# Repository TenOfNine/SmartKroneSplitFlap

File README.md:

# KRONE REW Fallblattanzeige — Ersatzsteuerung

Eigenbau-Steuerung für eine mechanische Fallblattanzeige der KRONE AG aus dem Jahr 1990. Die Original-Elektronik (Anzeigersteuerung und Palettensteuerungen PST mit HMCS44C) wird ersetzt. Mechanik und Anzeigenplatinen bleiben unverändert.

## Aufbau

```
ESP32-C3 (Master, WLAN/REST/MQTT)
  └─ RS-485 half duplex + CHAIN
       ├─ Daughter Card 1 (ATtiny1616) ── Anzeigenmodul 1
       ├─ Daughter Card 2 ────────────── Anzeigenmodul 2
       └─ …                                        bis 10
```

Jedes Anzeigenmodul erhält eine eigene kleine Steuerplatine, die die Hall-Impulse zählt, den Triac ansteuert und die aktuelle Blattposition kennt. Die Adressvergabe erfolgt automatisch entlang einer CHAIN-Leitung, sodass die Adresse der physischen Position entspricht und ein Kartentausch keine Einstellung erfordert.

## Eckdaten

| Größe | Wert |
|---|---|
| Anzeigenmodule | 10, Palettenmodulreihe A, Modulgröße 1 |
| Blätter je Modul | 40 |
| Zeichensatz | Leerbild, 0–9, A–Z, `-`, `.` |
| Zeit je Blatt | 60 ms, volle Umdrehung 2,40 s |
| Motor | Berger RSM 42/12, 42 V~, 250 U/min |
| Triac | Teccor L201E3, sensitives Gate |
| Modul-CPU | ATtiny1616 |
| Bus | RS-485, 115200 Bd, TP8485E |
| Master | ESP32-C3 Super Mini auf Trägerboard |

## Verzeichnisse

| Pfad | Inhalt |
|---|---|
| `docs/` | Spezifikation, Schaltpläne, Backlog, Toolchain, Symbolprüfungen, Prüfpunkte, Messprotokolle |
| `hardware/daughtercard/` | KiCad-Projekt der Modulsteuerung (geroutet, Fertigungspaket) |
| `hardware/master/` | KiCad-Projekt der Zentralsteuerung (geroutet, Fertigungspaket) |
| `firmware/module/` | ATtiny1616, PlatformIO |
| `firmware/master/` | ESP32-C3, PlatformIO (inkl. Web-UI, `prebuilt/` Flash-Image) |
| `tools/` | Setup, Schaltplan-/PCB-Generatoren, Router-Anbindung, Bus-Testwerkzeug |
| `reference/` | **Nicht versioniert.** Ablage für die Original-Herstellerunterlagen. |

## Stand

| Bereich | Stand |
|---|---|
| Spezifikation, Schaltplan (Netzliste) | vollständig, `docs/` |
| Schaltplan `.kicad_sch` + Footprints + PCB-Netzliste | generiert, ERC 0/0 (Daughter Card + Master) |
| PCB-Layout `.kicad_pcb` | geroutet, DRC 0 Fehler (in der CI geprüft); Daughter Cards und Zentralsteuerung gefertigt, Inbetriebnahme am Gerät läuft (`docs/progress.md`) |
| Modul-Firmware (ATtiny1616) | `firmware/module/`, Version siehe `firmware/CHANGELOG.md`; Bootloader für die Verteilung über den Bus |
| Master-Firmware (ESP32-C3 Super Mini) | `firmware/master/`, Web-UI, REST, MQTT, OTA — Web-Flasher siehe unten |
| Bus-Werkzeug | `tools/busctl.py` |
| CI | `.github/workflows/ci.yml`: Host-Tests, Firmware-Builds mit Abgleich der Prebuilts gegen die Quelle, ERC/DRC, Release-Paket je Tag |
| Offene Messungen O-2, O-5, O-6 | parametrisiert, blockieren die Fertigung nicht |

Der Projektstand für den Einstieg in eine neue Arbeitssitzung steht in
`docs/projektstand.md`.

## Einstieg

```bash
bash tools/setup.sh                              # Toolchain, siehe docs/toolchain.md
source .venv/bin/activate

pio test -e native -d firmware/module            # 163 Tests
pio test -e native -d firmware/master            # 137 Tests
python tools/test_busctl.py                      # 16 Tests + Rahmen-Selbsttest
python tools/gen_daughtercard_sch.py --erc --pdf --png
```

## Firmware flashen

**Master (ESP32-C3 Super Mini).** Am einfachsten über den Browser-Flasher:
**<https://tenofnine.github.io/SmartKroneSplitFlap/>**

Nötig: Chrome oder Edge auf dem Desktop, ein USB-C-Kabel **mit Datenadern** an
die Buchse des Moduls. „Modul verbinden & flashen" drücken — der C3 geht selbst
in den Download-Modus, kein BOOT-Taster. Nach dem Flashen öffnet die Karte den
Access-Point `krone_anzeige` für die WLAN-Zugangsdaten. Das fertige Image liegt
committet unter `firmware/master/prebuilt/`; neu bauen mit
`python tools/build_master_firmware.py` oder direkt
`pio run -e esp32c3 -t upload -d firmware/master`.

Die Web-Oberfläche vorab ansehen — dieselbe Seite mit Beispieldaten und
simuliertem Bus, ohne Gerät:
**<https://tenofnine.github.io/SmartKroneSplitFlap/demo/>**
(erzeugt aus `firmware/master/src/main.cpp` per `python tools/build_webui_demo.py`).

Spätere Updates laufen über die Web-UI (*Einstellungen › Firmware aktualisieren*):
den **signierten Container** `firmware/master/prebuilt/krone-master-esp32c3.kota`
hochladen. Das Modul verlangt eine gültige ECDSA-Signatur des Projektschlüssels —
Einrichtung siehe [`docs/firmware-signing.md`](docs/firmware-signing.md). Der
Zugriff auf Web-UI/REST ist ab Werk auf private Netze beschränkt und lässt sich
mit einem Passwort schützen (*Einstellungen › Zugriffsschutz*).

**Daughter Card (ATtiny1616).** Über die UPDI-Stiftleiste J6 mit einem
USB-Seriell-Adapter (FTDI/CP2102/CH340, **auf 5 V**) und einem 4,7-kΩ-Widerstand
zwischen TXD und RXD:

```
  USB-Seriell-Adapter                       Daughter Card J6 (1×3)
  ┌───────────────┐
  │           GND ●──────────────────────────────● 1  GND
  │           TXD ●────[ 4,7 kΩ ]───┬────────────● 2  UPDI   (→ ATtiny PA0)
  │           RXD ●─────────────────┘
  │        5V/VCC ●──────────────────────────────● 3  +5V
  └───────────────┘        └─ nur wenn die Karte sonst keine 5 V hat
```

An UPDI kein Kondensator (Schaltplan 4.4). Dann:

- **Browser:** <https://tenofnine.github.io/SmartKroneSplitFlap/>,
  Tab *Daughter Card* — Werksflash (Bootloader + App + `BOOTEND`-Fuse).
  **Am Gerät verifiziert** (10.09.2026): Chip-Erase, Geräte-ID-Prüfung, Fuse-
  und Seitenschreiben sowie die Bootloader→App-Übergabe laufen auf echter
  Hardware durch.
- **Sicher:** `pio run -e attiny1616 -t upload -d firmware/module` (Protokoll
  `serialupdi`, Port ggf. per `--upload-port`).

Das committete Image liegt unter `firmware/module/prebuilt/`; neu bauen mit
`python tools/build_module_firmware.py`.

## Ausblick

**Modul-Firmware über den Bus verteilen** — die Master-Steuerung flasht die
Daughter Cards aus ihrer Web-UI, ohne PC und Adapter.

- **Residenter Bootloader (umgesetzt, experimentell).** `firmware/bootloader/`
  liegt im per Fuse `BOOTEND = 0x0C` abgetrennten Boot-Bereich (App ab 0x0C00,
  env `attiny1616_boot`). Bei jedem Reset läuft er zuerst, startet die App oder
  empfängt eine neue über den Bus (`ENTER_BOOTLOADER` → `FW_BEGIN`/`_DATA`/`_END`).
  Einzeln adressierbar, ausfallsicher (abgebrochene Updates sind wiederholbar,
  der Bootloader bleibt intakt). Der Master trägt die signierte Modul-Firmware
  eingebettet und verteilt sie aus *Einstellungen › Modul-Firmware*
  („Alle aktualisieren"). Erstflash von Bootloader + App + Fuse über den
  Browser-Werksflasher (Tab „Daughter Card") oder UPDI — **das Werksflashen
  selbst und die Bootloader→App-Übergabe sind am Gerät verifiziert**
  (10.09.2026). `BOOTEND` sperrt den Baustein nicht. Die **Verteilung über den
  Bus** (Master erkennt/aktualisiert die Modul-Firmware) ist noch nicht
  getestet — Design und Bench-Test-Checkliste in
  [`docs/module-bootloader.md`](docs/module-bootloader.md); bis dahin
  `pio run -e attiny1616 -t upload` (ohne Bootloader) als abgesicherter Weg – ab Firmware 1.16 (setzt bei `BOOTEND≠0` selbst IVSEL); ältere Plain-Apps auf einer werksgeflashten Karte (BOOTEND=0x0C) legen die Interrupts lahm – Issue #19.
- **UPDI-Ader im Flachbandkabel (verworfener Bastelweg).** Ader 9 des Busbands
  ist frei; eine Drahtbrücke je Karte von `J6.2` auf `J2.9` brächte UPDI auf den
  Bus, aber allen zehn Karten gemeinsam (kein Einzeladressieren). Der
  Bootloader-Weg ist die bessere Lösung.

## Hinweis zu den Originalunterlagen

Die technische Dokumentation der KRONE AG ist urheberrechtlich geschützt und trägt einen ausdrücklichen Vervielfältigungsvorbehalt. Sie gehört nach `reference/` und ist über `.gitignore` von der Versionierung ausgenommen. In den Dokumenten dieses Repositories wird auf Zeichnungsnummern verwiesen, nicht aus den Unterlagen zitiert.

Alle eigenen Inhalte — Spezifikation, Schaltplan, Firmware, Messprotokolle, Fotos der eigenen Hardware — sind davon nicht betroffen.

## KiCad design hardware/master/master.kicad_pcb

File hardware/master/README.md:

# hardware/master

KiCad-Projekt der Zentralsteuerung (RS-485-Master, eine je Anlage).
**Stand:** Rev. 0.2 **fertig** — geroutet + GUI-Feinlayout (2 Lagen, ERC 0/0,
DRC 0/0/0), Symbolprüfung freigegeben, Fertigungspaket committet unter
`manufacturing/`. **Bereit zur Bestellung.** Rev. 0.2 = Eingangsschutz
(Verpol-P-FET Q1 + R8, RS-485-TVS D2) + Silk (+/- an J1, „ANT"-Text raus,
Referenztexte U2/D2/R4 am Bauteil). Die `master.kicad_pcb` ist der finale
Stand des Betreibers — nicht mehr per Skript regenerieren.

## Schnellcheck

3D-Vorschau (`tools/gen_master_pcb.py --render`):

| Oberseite | Unterseite |
|---|---|
|  |  |

Vollauflösung Schaltplan: [`docs/master.pdf`](../../docs/master.pdf) ·
ERC: 0 Fehler / 0 Warnungen (`gen_master_sch.py --erc`, in der CI geprüft) ·
DRC: 0 Fehler / 0 Warnungen / 0 unverdrahtet (Rev. 0.2). Feinlayout im GUI
(Bahnführung, Bestückungsdruck) ist Sache des Betreibers.

## Dateien

| Datei | Herkunft |
|---|---|
| `symbols/krone_master.kicad_sym` | **generiert** von `tools/build_krone_master_symbols.py`. Die 13 im Schaltplan verwendeten Symbole: Standardteile abgeflacht aus der KiCad-9-Bibliothek, `TP8485E-SR` wie bei der Daughter Card zusammengesetzt, `ESP32-C3-SuperMini` (16-Pin-Modul, 2×8) von Hand. Nicht bearbeiten. |
| `sym-lib-table` | projektlokale Bibliothekstabelle, bindet `krone_master` über `${KIPRJMOD}` ein |
| `footprints/logos.pretty/` | GitHub-Marke für die Rückseiten-Silkscreen (projektlokal, wie bei der Daughter Card) |
| `footprints/modules.pretty/` | `ESP32-C3-SuperMini.kicad_mod` — 2×8-THT für Buchsenleisten, Reihenabstand 15,24 mm, Pad 1 = 5V rechts oben, Antennen-Keepout an der Unterkante. Von Hand erstellt (kein Standard-Footprint). |
| `fp-lib-table` | projektlokale Footprint-Tabelle für die beiden `.pretty`-Ordner |
| `master.kicad_sch` | **generiert** von `tools/gen_master_sch.py` aus Netzliste (`docs/schaltplan-master.md` Kap. 6) und Footprint-Tabelle. 32 Bauteile, 20 Netze. |
| `master.kicad_pro` | Projektfile: projektlokale `sym-lib-table` / `fp-lib-table` + Netzklassen (Default, Power, GND — **kein AC**) aus Schaltplan Kap. 8 |
| `master.kicad_pcb` | Rev. 0.1: **Erstplatzierung** `tools/gen_master_pcb.py` + FreeRouting (`route_master.py`). Rev. 0.2 (Q1/R8/D2): **inkrementell** mit `tools/patch_master_pcb.py` in die geroutete Rev-0.1-Platine eingesetzt und mit `finish_routes.py` geschlossen (FreeRouting 2.3.0 hängt hier reproduzierbar). Maker-Mark / schwarz-weiß-Lagenaufbau von `tools/add_silk_marks.py --board …`. DRC 0/0. |
| `manufacturing/` | committetes Fertigungspaket (Gerber, Bohrdatei, Zip, BOM, CPL, README) von `tools/gen_master_manufacturing.py`. |
| `master.net` | **generiert** (`--netlist`), nicht versioniert. PCB-Netzliste. |

## Neu erzeugen

```bash
source .venv/bin/activate
python tools/build_krone_master_symbols.py                          # nur bei Änderung der Symbolauswahl
xvfb-run -a python tools/gen_master_sch.py --erc --pdf --png --netlist
```

**Vorsicht bei der `.kicad_pcb`:** Die Generatoren vergeben bei jedem Lauf neue
UUIDs. Solange die Platine noch nicht platziert/geroutet ist, gilt: `.kicad_sch`
+ `.kicad_pcb` nach einer Netzlistenänderung gemeinsam neu erzeugen und committen.
**Sobald die `.kicad_pcb` geroutet ist** (aktueller Stand), wird sie **nicht**
neu erzeugt — `tools/gen_master_pcb.py` verweigert den Neubau, wenn Bahnen oder
Zonen vorhanden sind (`--force`-Schutz). Eine Netzlistenänderung erfordert
stattdessen ein UUID-Remapping der Footprint-Pfade und danach
`tools/route_master.py`. Details: `docs/layout-master.md`.

| Flag (`gen_master_sch.py`) | Ausgabe |
|---|---|
| `--erc` | `docs/erc-master.rpt` |
| `--pdf` | `docs/master.pdf` |
| `--png` | `docs/master.png` (Vorschau ohne Rahmen, für GitHub) |
| `--netlist` | `master.net` (PCB-Netzliste, nicht versioniert) |

`--check-only` (bzw. `--check` bei `build_krone_master_symbols.py`) prüft ohne zu
schreiben — für die CI (T10). Der Check umfasst: jeder Pin an genau einem Netz
oder NC, jedes Bauteil mit vorhandenem Footprint.

Netznamen tragen im Netlist-Export das KiCad-übliche Wurzelblatt-Präfix (`/+5V`,
`/GND` …), weil die Rails über lokale Labels laufen. Für den PCB-Import ist das
unerheblich.

## Zum Schaltplan

Die Verbindungen werden über **gleichnamige lokale Labels an den Pins** hergestellt,
nicht über gezeichnete Leitungen. Die Bauteile liegen in einem groben Raster, nicht
handverlegt. Das ist bewusst so:

- Die menschenlesbare Darstellung der Schaltung ist `docs/schaltplan-master.md`
  Kapitel 5 (Prinzipschaltbilder) und Kapitel 6 (verbindliche Netzliste).
- Die `.kicad_sch` ist das maschinell erzeugte Abbild von Kapitel 6 für ERC,
  Netzlistenexport und das Layout.

## Layout und Routing

Footprints sind allen 32 Bauteilen zugeordnet (`FOOTPRINTS` in
`tools/gen_master_sch.py`). Die Platine ist geroutet — Erstplatzierung, Zonen,
Netzklassen (alle Bahnen 0,5 mm, Power `+5V(_RAW/_IN)`/`+3V3`/`+15V`/`ADER9`
0,8 mm mit 0,8-mm-Vias), Masseflächen F.Cu + B.Cu mit 5-mm-Stitching und die
offenen Punkte mit Layoutbezug stehen in
[`docs/layout-master.md`](../../docs/layout-master.md).
Die Massefläche ist nur im Antennenbereich unter U1 ausgespart (Footprint-Keepout).
Die JLCPCB-Bestückung beschreibt [`manufacturing/README.md`](manufacturing/README.md):
18 SMD-Teile (0805 / SOIC-8 / SOT-23 / SOT-23-5), alle LCSC-Basic; J1–J4,
U1-Sockel und JP1 von Hand.

## Prüfpunkte

`docs/symbolpruefung-master.md` ist vom Betreiber **freigegeben** (01.09.2026):
74LVC1G17 gegen Nexperia Rev. 16.1 §6.1, ESP32-C3-Modul-Pinbelegung und
Einbaulage aus den Betreiberfotos, TP8485E per Verweis. **Rev. 0.2 nachgetragen,
Freigabe offen:** AO3401A (SOT-23 1=G/2=S/3=D) und SM712 (Pin 3 = GND, gegen
Bourns-CDSOT23-SM712-Datenblatt).

Offen (blockieren die Fertigung nicht bzw. sind vor der Bestellung zu klären):

| Nr | Punkt | Wirkung |
|---|---|---|
| M-2 | Aufwärtswandler-IC + Pinbelegung | Boost-Steckplatz J4 bleibt DNP, bis O-2 gemessen ist |
| M-3 | CHAIN 3,3 V → 5 V | **entschieden:** U3 wird bestückt, R7 (0 Ω) DNP-Reserveplatz |
| M-4 | RS-485-TVS D2 (SM712/PSM712) | Pinbelegung gegen Bourns-Datenblatt geprüft; ProTek-Spot-Check + Freigabe vor Bestellung |
| O-2 | 5 V oder 12–20 V an Anzeige-Pin 9 | ob JP1 auf +15 V steht und der Boost bestückt wird |

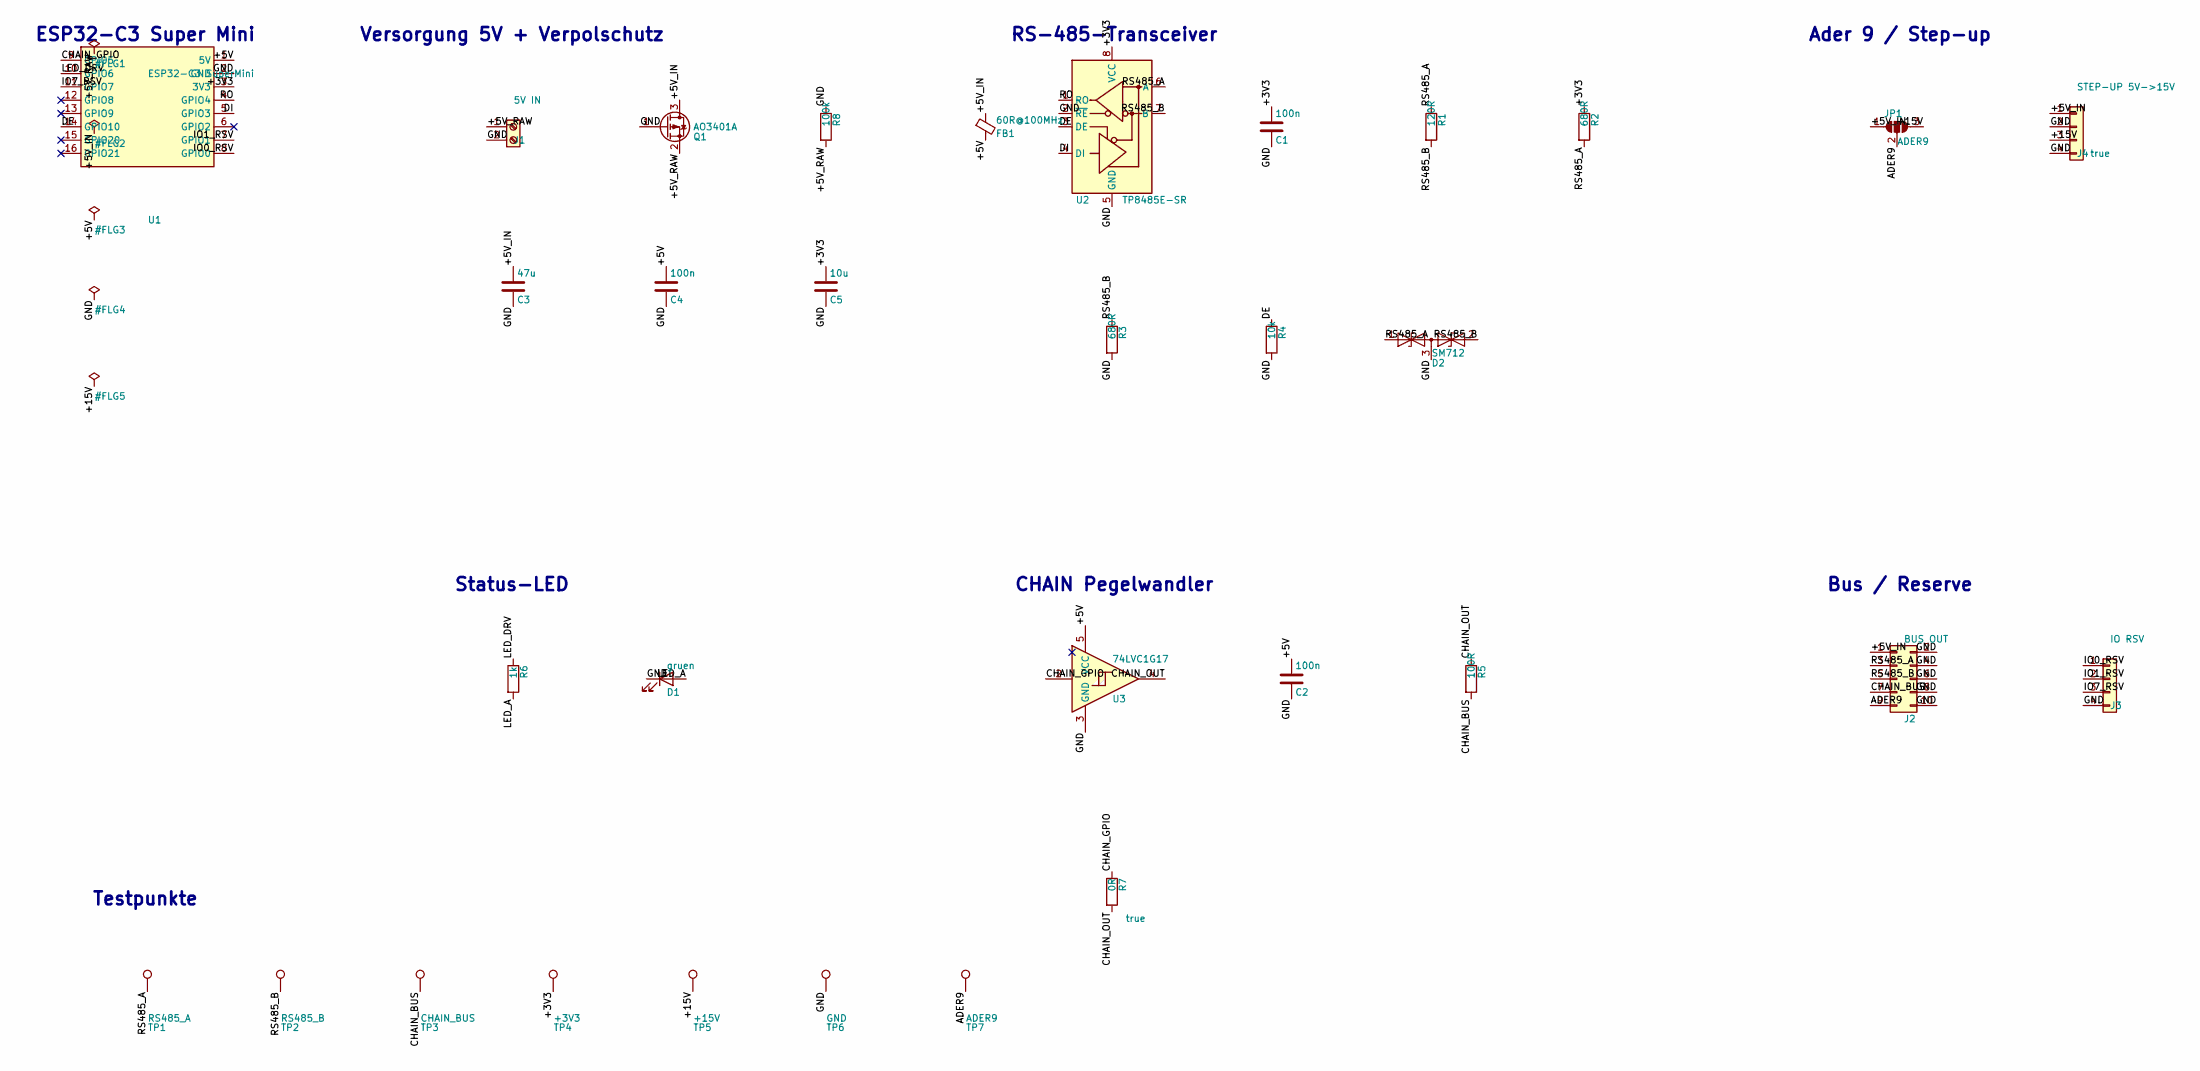
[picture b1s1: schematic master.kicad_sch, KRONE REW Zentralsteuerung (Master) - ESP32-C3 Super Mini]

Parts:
C1, C2, C4: 100n; C_0805_2012Metric
C3: 47u; C_1206_3216Metric
C5: 10u; C_0805_2012Metric
D1: gruen; LED_0805_2012Metric
D2: SM712; SOT-23
FB1: 60R@100MHz; L_0805_2012Metric
J1: 5V IN; TerminalBlock_Phoenix_MKDS-1,5-2-5.08_1x02_P5.08mm_Horizont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
J2: BUS OUT; IDC-Header_2x05_P2.54mm_Vertical
J3: IO RSV; PinHeader_1x04_P2.54mm_Vertical
J4: STEP-UP 5V->15V; PinHeader_1x04_P2.54mm_Vertical
JP1: ADER9; SolderJumper-3_P1.3mm_Open_Pad1.0x1.5mm
Q1: AO3401A; SOT-23
R1: 120R; R_0805_2012Metric
R2, R3: 680R; R_0805_2012Metric
R4: 10k; R_0805_2012Metric
R5: 100R; R_0805_2012Metric
R6: 1k; R_0805_2012Metric
R7: 0R; R_0805_2012Metric
R8: 100k; R_0805_2012Metric
TP1: RS485_A; TestPoint_Pad_D1.5mm
TP2: RS485_B; TestPoint_Pad_D1.5mm
TP3: CHAIN_BUS; TestPoint_Pad_D1.5mm
TP4: +3V3; TestPoint_Pad_D1.5mm
TP5: +15V; TestPoint_Pad_D1.5mm
TP6: GND; TestPoint_Pad_D1.5mm
TP7: ADER9; TestPoint_Pad_D1.5mm
U1: ESP32-C3 SuperMini; ESP32-C3-SuperMini
U2: TP8485E-SR; SOIC-8_3.9x4.9mm_P1.27mm
U3: 74LVC1G17; SOT-23-5

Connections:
/+3V3: C1.1, C5.1, R2.1, TP4.1, U1.3 (3V3), U2.8 (VCC)
/+5V: C2.1, C4.1, FB1.2, U1.1 (5V), U3.5 (VCC)
/+5V_IN: C3.1, FB1.1, J2.1, J4.1, JP1.1 (A), Q1.3 (D)
/+5V_RAW: J1.1, Q1.2 (S), R8.2
/+15V: J4.3, JP1.3 (B), TP5.1
/ADER9: J2.9, JP1.2 (C), TP7.1
/CHAIN_BUS: J2.7, R5.2, TP3.1
/CHAIN_GPIO: R7.1, U1.9 (GPIO5), U3.2
/CHAIN_OUT: R5.1, R7.2, U3.4
/DE: R4.1, U1.14 (GPIO10), U2.3 (DE)
/DI: U1.5 (GPIO3), U2.4 (DI)
/GND: C1.2, C2.2, C3.2, C4.2, C5.2, D1.1 (K), D2.3 (common), J1.2, J2.2, J2.4, J2.6, J2.8, J2.10, J3.4, J4.2, J4.4, Q1.1 (G), R3.2, R4.2, R8.1, TP6.1, U1.2 (GND), U2.2 (~RE), U2.5 (GND), U3.3 (GND)
/IO0_RSV: J3.1, U1.8 (GPIO0)
/IO1_RSV: J3.2, U1.7 (GPIO1)
/IO7_RSV: J3.3, U1.11 (GPIO7)
/LED_A: D1.2 (A), R6.2
/LED_DRV: R6.1, U1.10 (GPIO6)
/RO: U1.4 (GPIO4), U2.1 (RO)
/RS485_A: D2.1 (A1), J2.3, R1.1, R2.2, TP1.1, U2.6 (A)
/RS485_B: D2.2 (A2), J2.5, R1.2, R3.1, TP2.1, U2.7 (B)

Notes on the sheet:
ESP32-C3 Super Mini
Versorgung 5V + Verpolschutz
RS-485-Transceiver
CHAIN Pegelwandler
Status-LED
Ader 9 / Step-up
Bus / Reserve
Testpunkte

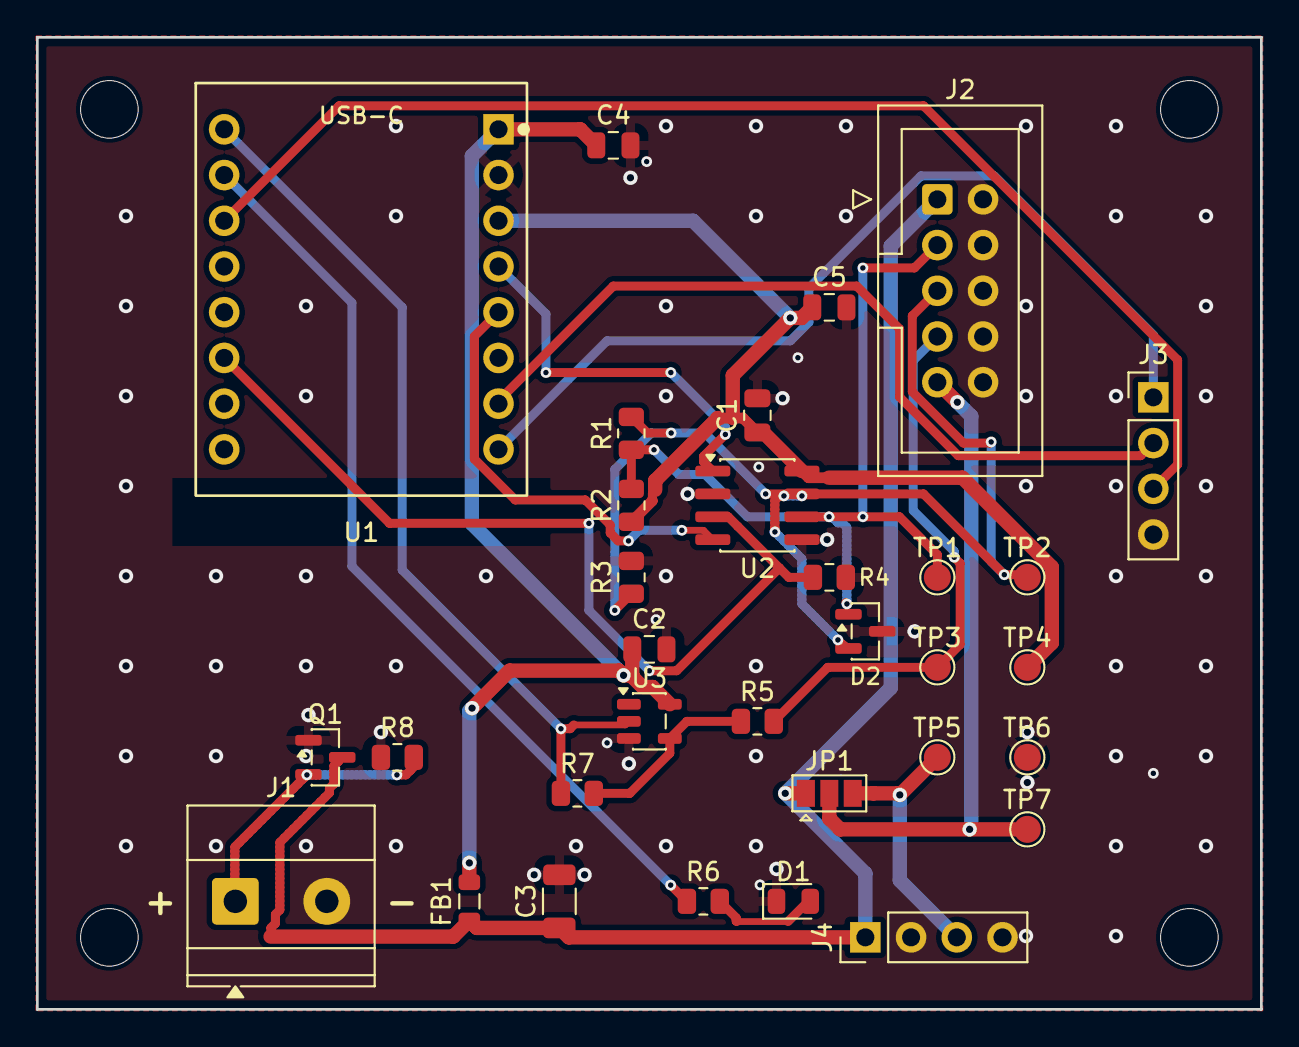
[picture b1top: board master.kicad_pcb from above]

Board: 2 copper layers, 68.0 x 54.0 mm, 37 parts (1 on the bottom side), 20 nets.

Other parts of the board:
GH1: Logo_GitHub
H1, H2, H3, H4: MountingHole_3.2mm_M3

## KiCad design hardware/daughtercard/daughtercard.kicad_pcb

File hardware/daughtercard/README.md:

# hardware/daughtercard

KiCad-Projekt der Modulsteuerung (eine je Anzeigenmodul).
**Stand:** geroutet (2 Lagen, DRC 0 Fehler), Fertigungspaket committet unter
`manufacturing/`, bei JLCPCB in Auftrag.

## Schnellcheck

3D-Vorschau (`tools/gen_daughtercard_pcb.py --render`):

| Oberseite | Unterseite |
|---|---|
|  |  |

Vollauflösung Schaltplan: [`docs/daughtercard.pdf`](../../docs/daughtercard.pdf) ·
ERC: 0 Fehler / 0 Warnungen (`gen_daughtercard_sch.py --erc`, in der CI geprüft)

## Dateien

| Datei | Herkunft |
|---|---|
| `symbols/krone.kicad_sym` | **generiert** von `tools/build_krone_symbols.py` aus der KiCad-9-Bibliothek. Alle 15 im Schaltplan verwendeten Symbole, abgeflacht. Nicht von Hand bearbeiten. |
| `sym-lib-table` | projektlokale Bibliothekstabelle, bindet `krone` über `${KIPRJMOD}` ein |
| `daughtercard.kicad_sch` | **generiert** von `tools/gen_daughtercard_sch.py` aus Netzliste (`docs/schaltplan-daughtercard.md` Kap. 6) und Footprint-Tabelle (T5) |
| `daughtercard.kicad_pro` | Projektfile: projektlokale `sym-lib-table` + Netzklassen (AC, RS485, Power) aus Schaltplan Kap. 8.2 |
| `daughtercard.kicad_pcb` | **Erstplatzierung** von `tools/gen_daughtercard_pcb.py` (System-Python, `pcbnew`), danach vom Betreiber feinjustiert und mit `tools/route_daughtercard.py` (FreeRouting + `finish_routes.py` + Masseflächen) verdrahtet. Maker-Mark / schwarz-weiß-Lagenaufbau von `tools/add_silk_marks.py`. |
| `manufacturing/` | committetes Fertigungspaket (Gerber, Bohrdatei, Zip, BOM, CPL, README) von `tools/gen_manufacturing.py`. |
| `daughtercard.net` | **generiert** (`--netlist`), nicht versioniert. PCB-Netzliste. |

## Neu erzeugen

```bash
source .venv/bin/activate
python tools/build_krone_symbols.py                            # nur bei Änderung der Symbolauswahl
python tools/gen_daughtercard_sch.py --erc --pdf --png --netlist
```

**Vorsicht bei der `.kicad_pcb`:** Die Generatoren vergeben bei jedem Lauf neue
UUIDs. Solange die Platine noch nicht platziert/geroutet ist, gilt: `.kicad_sch`
+ `.kicad_pcb` nach einer Netzlistenänderung gemeinsam neu erzeugen und committen.
**Sobald die `.kicad_pcb` platziert/geroutet ist** (aktueller Stand), wird sie
**nicht** neu erzeugt — eine Netzlistenänderung erfordert stattdessen ein
UUID-Remapping der Footprint-Pfade (siehe Commit „F1 → 0-Ω-Brücke") und danach
`tools/route_daughtercard.py`. Details: `docs/layout-daughtercard.md`.

| Flag | Ausgabe |
|---|---|
| `--erc` | `docs/erc-daughtercard.rpt` |
| `--pdf` | `docs/daughtercard.pdf` |
| `--png` | `docs/daughtercard.png` (Vorschau ohne Rahmen, für GitHub) |
| `--netlist` | `daughtercard.net` (PCB-Netzliste, nicht versioniert) |

`--check-only` (bzw. `--check` bei `build_krone_symbols.py`) prüft ohne zu schreiben —
für die CI (T10). Der Check umfasst: jeder Pin an genau einem Netz oder NC, jedes
Bauteil mit vorhandenem Footprint.

Netznamen tragen im Netlist-Export das KiCad-übliche Wurzelblatt-Präfix (`/+5V`,
`/GND` …), weil die Rails über lokale Labels laufen. Für den PCB-Import ist das
unerheblich; wer es ohne Präfix will, stellt die Rails auf Power-Symbole um.

## Zum Schaltplan

Die Verbindungen werden über **gleichnamige lokale Labels an den Pins** hergestellt,
nicht über gezeichnete Leitungen. Die Bauteile liegen in einem groben Raster, nicht
handverlegt. Das ist bewusst so:

- Die menschenlesbare Darstellung der Schaltung ist `docs/schaltplan-daughtercard.md`
  Kapitel 5 (Prinzipschaltbilder) und Kapitel 6 (verbindliche Netzliste).
- Die `.kicad_sch` ist das maschinell erzeugte Abbild von Kapitel 6 für ERC,
  Netzlistenexport und – nach dem Footprint-Schritt T5 – das Layout.

Eine handverlegte, ablesbare Schaltplanseite kann später folgen; sie ist nicht
Teil von T4.

## Layout (T5) und Routing

Footprints sind allen 48 Bauteilen zugeordnet (`FOOTPRINTS` in
`tools/gen_daughtercard_sch.py`). Die Platine ist geroutet — Zonen, Netzklassen
(alle Bahnen 0,5 mm außer AC 1,5 mm), Masseflächen und die offenen Punkte mit
Layoutbezug stehen in [`docs/layout-daughtercard.md`](../../docs/layout-daughtercard.md),
die JLCPCB-Bestückung in [`docs/jlc-bestueckung.md`](../../docs/jlc-bestueckung.md).

## Prüfpunkte

Die zwei Netzlisten-Entscheidungen aus T4 (P-1 Testpads, P-2 BAT54S) sind vom
Betreiber freigegeben, siehe [`docs/pruefpunkte-t4.md`](../../docs/pruefpunkte-t4.md).

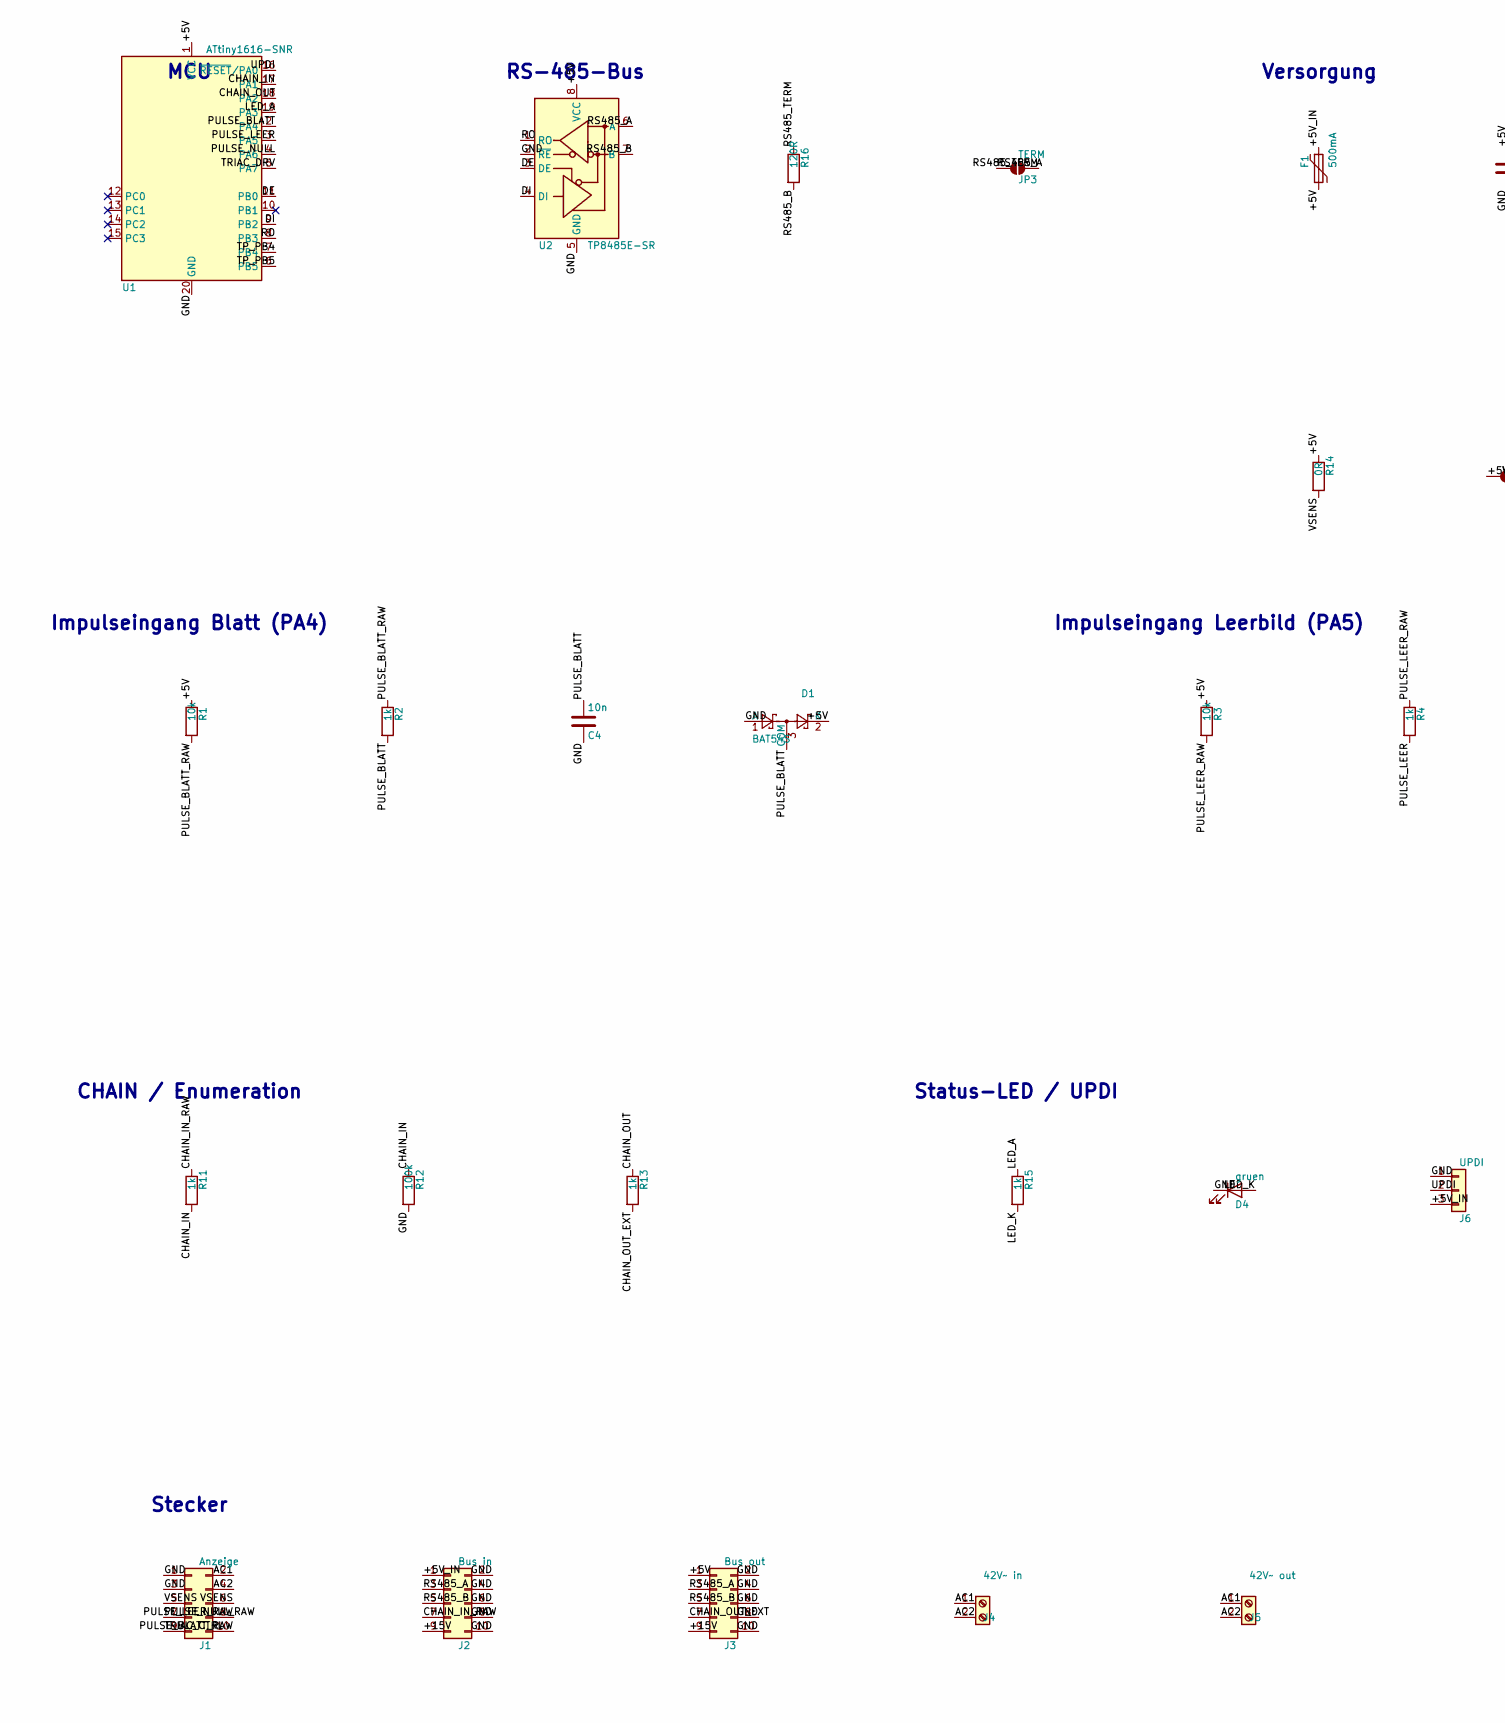
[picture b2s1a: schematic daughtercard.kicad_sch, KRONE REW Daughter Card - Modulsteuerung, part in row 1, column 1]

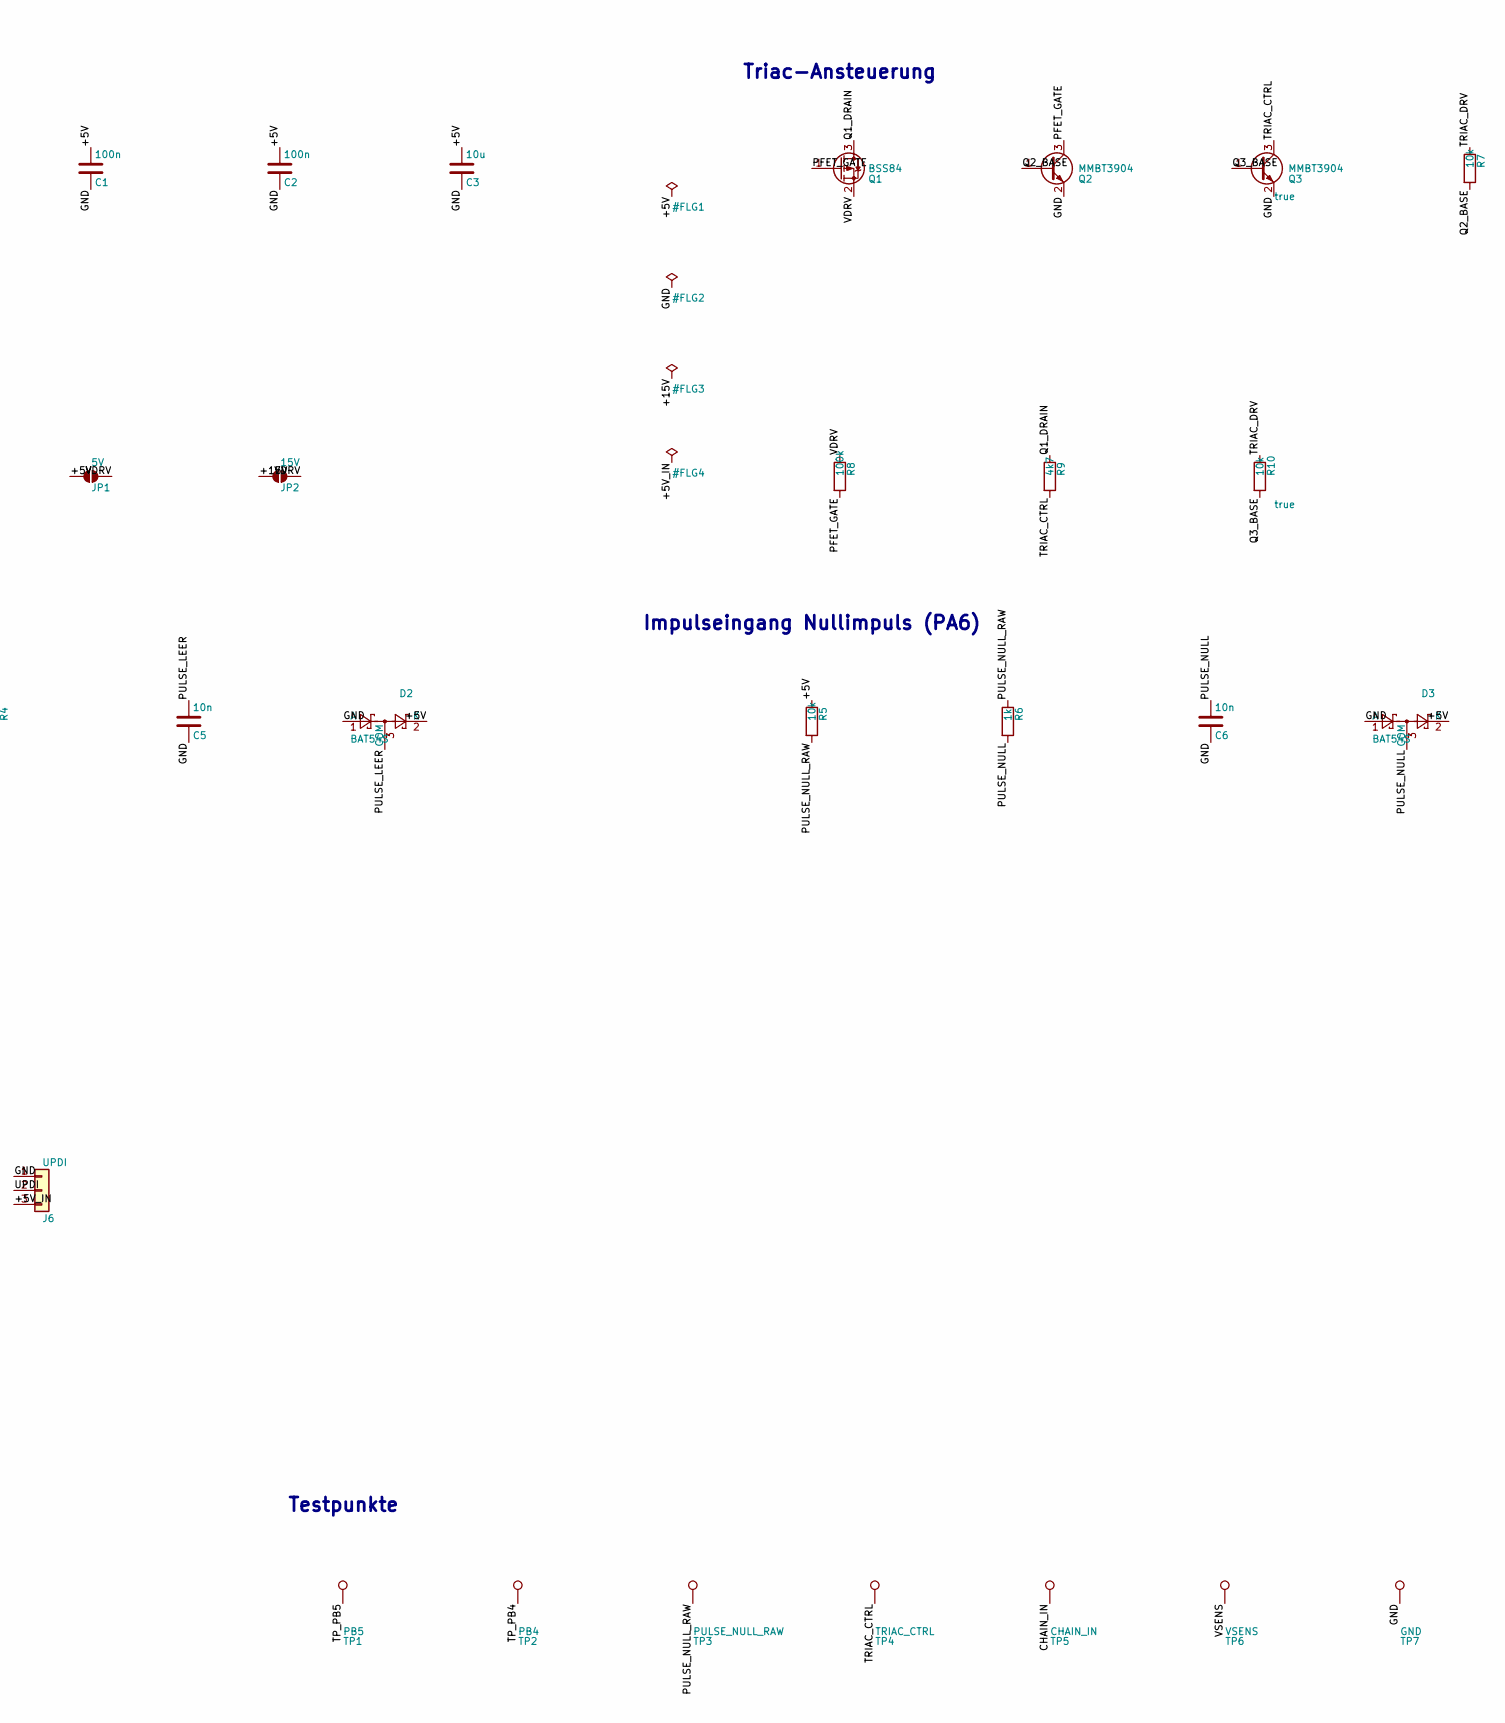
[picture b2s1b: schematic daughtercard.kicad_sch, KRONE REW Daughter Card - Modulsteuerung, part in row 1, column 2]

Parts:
C1, C2: 100n; C_0805_2012Metric
C3: 10u; C_1206_3216Metric
C4, C5, C6: 10n; C_0805_2012Metric
D1, D2, D3: BAT54S; SOT-23
D4: gruen; LED_0805_2012Metric
F1: 500mA; Fuse_1206_3216Metric
J1: Anzeige; PinSocket_2x05_P2.54mm_Vertical
J2: Bus in; IDC-Header_2x05_P2.54mm_Vertical
J3: Bus out; IDC-Header_2x05_P2.54mm_Vertical
J4: 42V~ in; TerminalBlock_Phoenix_MKDS-1,5-2-5.08_1x02_P5.08mm_Horizont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
J5: 42V~ out; TerminalBlock_Phoenix_MKDS-1,5-2-5.08_1x02_P5.08mm_Horizont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
J6: UPDI; PinHeader_1x03_P2.54mm_Vertical
JP1: 5V; SolderJumper-2_P1.3mm_Open_Pad1.0x1.5mm
JP2: 15V; SolderJumper-2_P1.3mm_Open_Pad1.0x1.5mm
JP3: TERM; SolderJumper-2_P1.3mm_Open_Pad1.0x1.5mm
Q1: BSS84; SOT-23
Q2, Q3: MMBT3904; SOT-23
R1, R3, R5, R7, R10: 10k; R_0805_2012Metric
R2, R4, R6, R11, R13, R15: 1k; R_0805_2012Metric
R8, R12: 100k; R_0805_2012Metric
R9: 4k7; R_0805_2012Metric
R14: 0R; R_1206_3216Metric
R16: 120R; R_0805_2012Metric
TP1: PB5; TestPoint_Pad_D1.5mm
TP2: PB4; TestPoint_Pad_D1.5mm
TP3: PULSE_NULL_RAW; TestPoint_Pad_D1.5mm
TP4: TRIAC_CTRL; TestPoint_Pad_D1.5mm
TP5: CHAIN_IN; TestPoint_Pad_D1.5mm
TP6: VSENS; TestPoint_Pad_D1.5mm
TP7: GND; TestPoint_Pad_D1.5mm
U1: ATtiny1616-SNR; SOIC-20W_7.5x12.8mm_P1.27mm
U2: TP8485E-SR; SOIC-8_3.9x4.9mm_P1.27mm

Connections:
/+5V: C1.1, C2.1, C3.1, D1.2 (K), D2.2 (K), D3.2 (K), F1.2, J3.1, JP1.1 (A), R1.1, R3.1, R5.1, R14.1, U1.1 (VCC), U2.8 (VCC)
/+5V_IN: F1.1, J2.1, J6.3
/+15V: J2.9, J3.9, JP2.1 (A)
/AC1: J1.2, J4.1, J5.1
/AC2: J1.4, J4.2, J5.2
/CHAIN_IN: R11.2, R12.1, TP5.1, U1.17 (PA1)
/CHAIN_IN_RAW: J2.7, R11.1
/CHAIN_OUT: R13.1, U1.18 (PA2)
/CHAIN_OUT_EXT: J3.7, R13.2
/DE: U1.11 (PB0), U2.3 (DE)
/DI: U1.9 (PB2), U2.4 (DI)
/GND: C1.2, C2.2, C3.2, C4.2, C5.2, C6.2, D1.1 (A), D2.1 (A), D3.1 (A), D4.1 (K), J1.1, J1.3, J2.2, J2.4, J2.6, J2.8, J2.10, J3.2, J3.4, J3.6, J3.8, J3.10, J6.1, Q2.2 (E), Q3.2 (E), R12.2, TP7.1, U1.20 (GND), U2.2 (~RE), U2.5 (GND)
/LED_A: R15.1, U1.19 (PA3)
/LED_K: D4.2 (A), R15.2
/PFET_GATE: Q1.1 (G), Q2.3 (C), R8.2
/PULSE_BLATT: C4.1, D1.3 (COM), R2.2, U1.2 (PA4)
/PULSE_BLATT_RAW: J1.10, R1.2, R2.1
/PULSE_LEER: C5.1, D2.3 (COM), R4.2, U1.3 (PA5)
/PULSE_LEER_RAW: J1.8, R3.2, R4.1
/PULSE_NULL: C6.1, D3.3 (COM), R6.2, U1.4 (PA6)
/PULSE_NULL_RAW: J1.7, R5.2, R6.1, TP3.1
/Q1_DRAIN: Q1.3 (D), R9.1
/Q2_BASE: Q2.1 (B), R7.2
/Q3_BASE: Q3.1 (B), R10.2
/RO: U1.8 (PB3), U2.1 (RO)
/RS485_A: J2.3, J3.3, JP3.1 (A), U2.6 (A)
/RS485_B: J2.5, J3.5, R16.2, U2.7 (B)
/RS485_TERM: JP3.2 (B), R16.1
/TP_PB4: TP2.1, U1.7 (PB4)
/TP_PB5: TP1.1, U1.6 (PB5)
/TRIAC_CTRL: J1.9, Q3.3 (C), R9.2, TP4.1
/TRIAC_DRV: R7.1, R10.1, U1.5 (PA7)
/UPDI: J6.2, U1.16 (~RESET/PA0)
/VDRV: JP1.2 (B), JP2.2 (B), Q1.2 (S), R8.1
/VSENS: J1.5, J1.6, R14.2, TP6.1

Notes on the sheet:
MCU
RS-485-Bus
Versorgung
Triac-Ansteuerung
Impulseingang Blatt (PA4)
Impulseingang Leerbild (PA5)
Impulseingang Nullimpuls (PA6)
CHAIN / Enumeration
Status-LED / UPDI
Stecker
Testpunkte

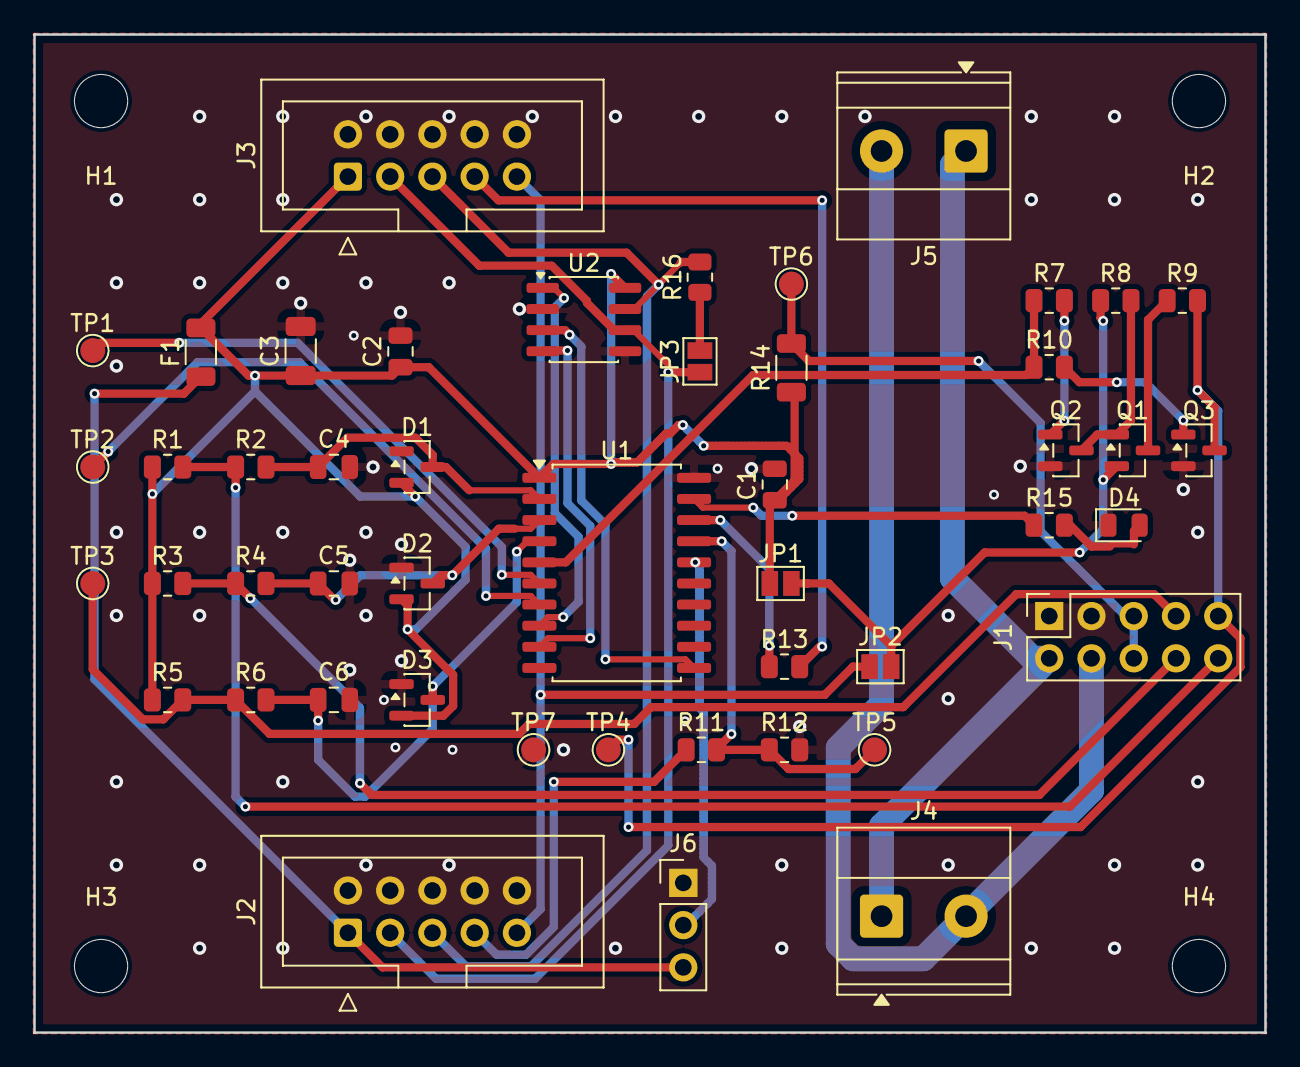
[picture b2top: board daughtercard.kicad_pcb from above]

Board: 2 copper layers, 74.0 x 60.0 mm, 53 parts (1 on the bottom side), 35 nets.

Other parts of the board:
GH1: Logo_GitHub
H1, H2, H3, H4: MountingHole_3.2mm_M3

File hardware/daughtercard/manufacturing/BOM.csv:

Comment,Designator,Footprint,LCSC Part #
0R,F1 R14,R_1206_3216Metric,C17888
100k,R8 R12,R_0805_2012Metric,C17407
100n,C1 C2,C_0805_2012Metric,C49678
10k,R1 R3 R5 R7,R_0805_2012Metric,C17414
10n,C4 C5 C6,C_0805_2012Metric,C1710
10u,C3,C_1206_3216Metric,C13585
120R,R16,R_0805_2012Metric,C17437
1k,R2 R4 R6 R11 R13 R15,R_0805_2012Metric,C17513
4k7,R9,R_0805_2012Metric,C17673
ATtiny1616-SNR,U1,SOIC-20W_7.5x12.8mm_P1.27mm,C614136
BAT54S,D1 D2 D3,SOT-23,
BSS84,Q1,SOT-23,
MMBT3904,Q2,SOT-23,C20526
TP8485E-SR,U2,SOIC-8_3.9x4.9mm_P1.27mm,C94206
gruen,D4,LED_0805_2012Metric,
